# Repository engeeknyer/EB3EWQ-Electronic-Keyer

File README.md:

# EB3EWQ Electronic Keyer

The EB3EWQ Electrònic Keyer is a project espeally designed for Amateur Radio. Consist in a single board containing electronics and the keyer itsef. Using printed touch sensor, it provides a high speed keying, because there's no mechanical parts that affect the operator speed.

This project contents:

  - The source code for programming the ATtiny
  - The schematic diagram for eagle cad (.sch)
  - The PCB design for eagle cad (.brd)

Program is uploaded to ATtiny using Arduino IDE. Can be tested in Arduino UNO board.

TODO: 

  - Program a monitor output, already wired in the board.
  - Provide a way to program tone monitor output, adjusting at init state.

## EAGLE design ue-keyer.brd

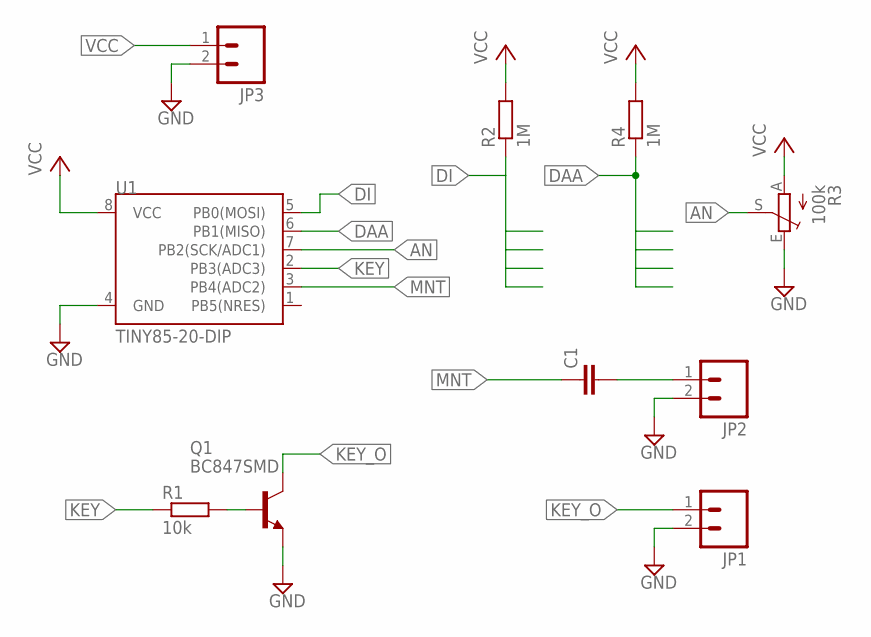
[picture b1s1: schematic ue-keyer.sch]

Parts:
C1: C-EUC1206; C1206
JP1, JP2, JP3: M02LOCK_LONGPADS; 1X02_LOCK_LONGPADS
Q1: BC847SMD; SOT23
R1: 10k; R0805
R2, R4: 1M; R0805
R3: 100k; ECP10S
U1: TINY85-20-DIP; DIP08

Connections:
AN: R3.S, U1.7 (PB2(SCK/ADC1))
DAA: R4.1, U1.6 (PB1(MISO))
DI: R2.1, U1.5 (PB0(MOSI))
GND: JP1.2, JP2.2, JP3.2, Q1.2 (E), R3.E, U1.4 (GND)
KEY: R1.1, U1.2 (PB3(ADC3))
KEY_O: JP1.1, Q1.3 (C)
MNT: C1.1, U1.3 (PB4(ADC2))
MNT_O: C1.2, JP2.1
unnamed: Q1.1 (B), R1.2
VCC: JP3.1, R2.2, R3.A, R4.2, U1.8 (VCC)

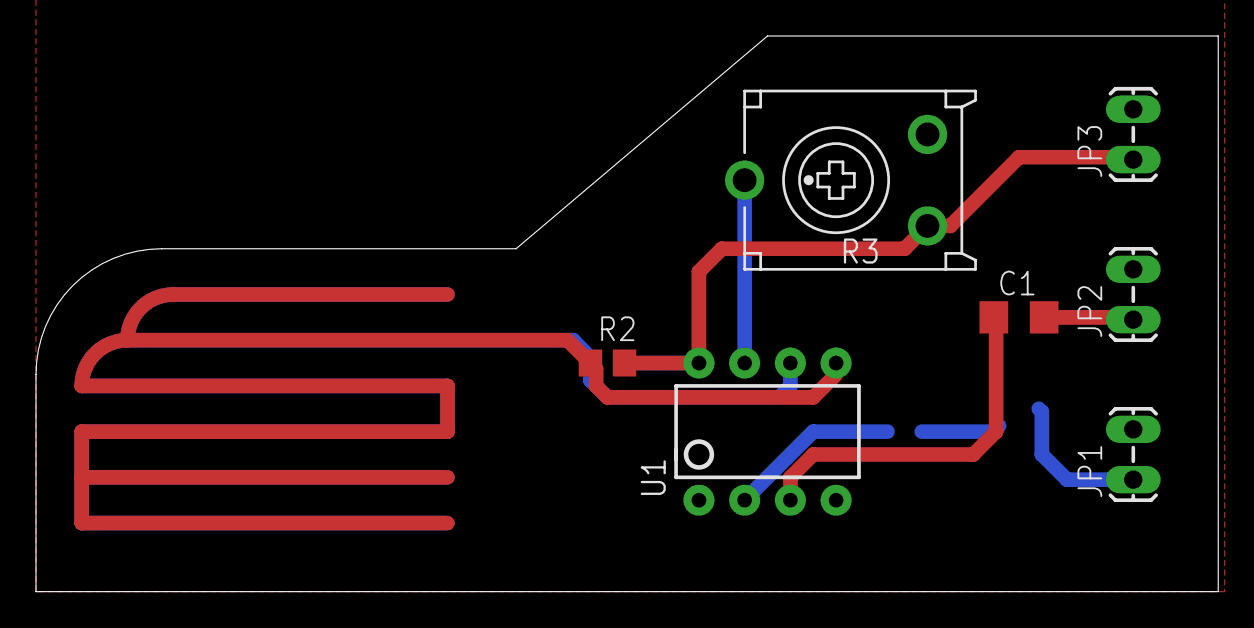
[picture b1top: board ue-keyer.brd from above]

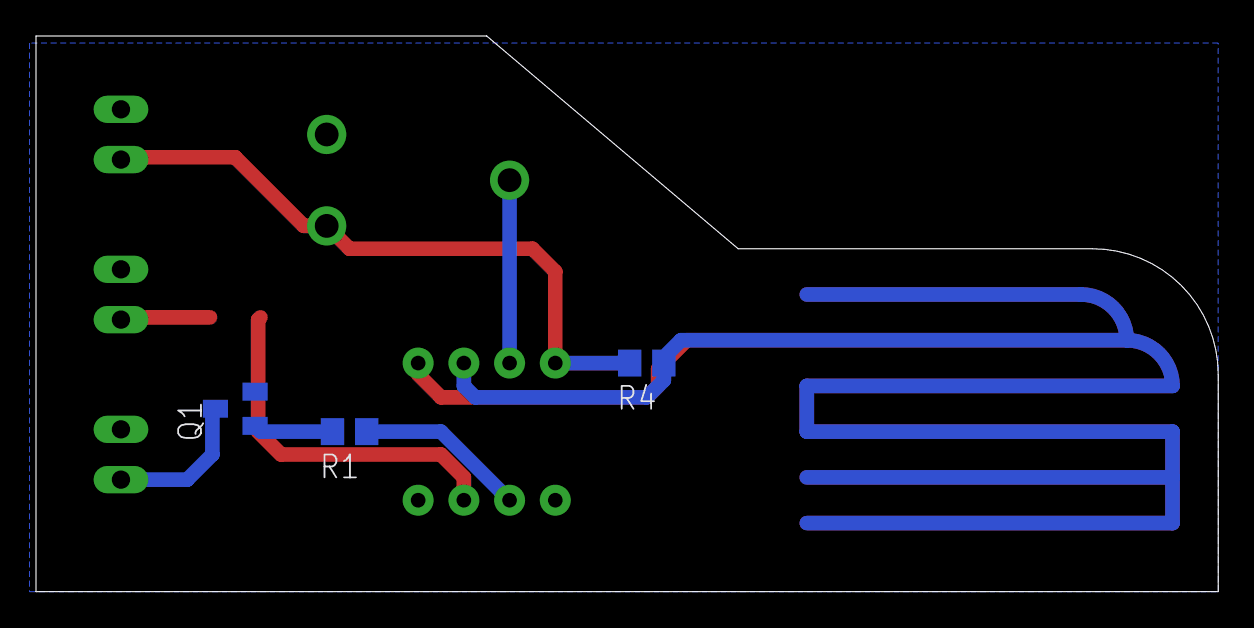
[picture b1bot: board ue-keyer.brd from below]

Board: 2 copper layers, 65.7 x 30.9 mm, 10 parts (3 on the bottom side), 10 nets.

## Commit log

2017-04-25 uploading files
2017-04-25 uploading files2
2017-04-25 Just a few mods in README

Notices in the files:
parts and their libraries:
SparkFun-Connectors: Licensing: Creative Commons ShareAlike 4.0 International - https://creativecommons.org/licenses/by-sa/4.0
